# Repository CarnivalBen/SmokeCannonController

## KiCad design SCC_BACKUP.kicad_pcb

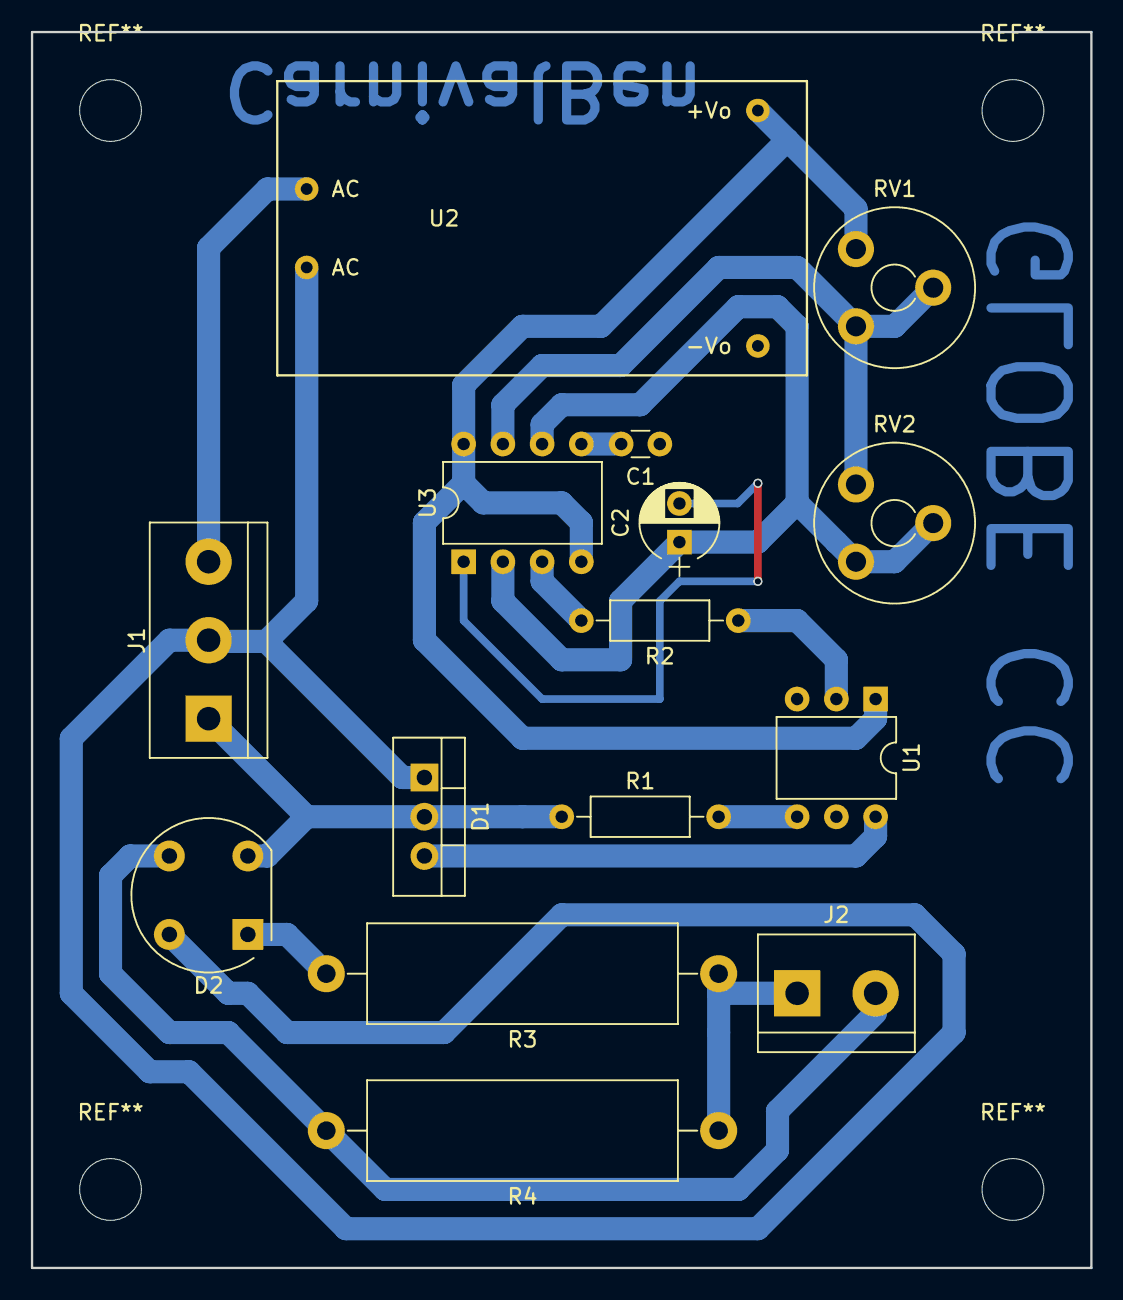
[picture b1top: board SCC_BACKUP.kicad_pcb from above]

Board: 2 copper layers, 68.6 x 80.0 mm, 15 parts (0 on the bottom side), 15 nets.

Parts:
C1: 0.01uF; C_Disc_D3.0mm_W1.6mm_P2.50mm
C2: 470uF; CP_Radial_D5.0mm_P2.50mm
D1: BTA08-600C; TO-220-3_Vertical
D2: D_Bridge_+-AA; Diode_Bridge_Round_D9.8mm
J1: SMOKE_MACHINE_XLR; TerminalBlock_bornier-3_P5.08mm
J2: LED_OUTPUT; TerminalBlock_bornier-2_P5.08mm
R1, R2: 100; R_Axial_DIN0207_L6.3mm_D2.5mm_P10.16mm_Horizontal
R3: 820; R_Axial_Power_L20.0mm_W6.4mm_P25.40mm
R4: 30; R_Axial_Power_L20.0mm_W6.4mm_P25.40mm
RV1: 100K; Potentiometer_Trimmer_Piher_PT-10v5_Horizontal_Px5.0mm_Py5.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
RV2: 1K; Potentiometer_Trimmer_Piher_PT-10v5_Horizontal_Px5.0mm_Py5.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
U1: MOC3020M; DIP-6_W7.62mm
U2: PSU-5VDC; HLK-PM01
U3: LM555; DIP-8_W7.62mm

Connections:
0V: C1.1, C2.2, U2.2, U3.1
5V: RV1.3, U1.1, U2.1, U3.4, U3.8
FEED: J1.3, U2.3
unnamed: C1.2, U3.5
unnamed: C2.1, RV2.1, RV2.2, U3.2, U3.6
unnamed: D1.3, U1.6
unnamed: D2.1, R3.2
unnamed: D2.3, J2.2, R4.2
unnamed: J2.1, R3.1, R4.1
unnamed: R1.2, U1.4
unnamed: R2.2, U3.3
unnamed: RV1.1, RV1.2, RV2.3, U3.7
PUMP: D1.2, D2.2, J1.1, R1.1
RETURN: D1.1, D2.4, J1.2, U2.4
TRIGGER: R2.1, U1.2

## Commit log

2018-04-16 Design version 1 done.
